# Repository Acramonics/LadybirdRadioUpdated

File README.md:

Making a Transistor Radio
=========================

Acramonics 2026
---------------

The Ladybird book *Making a Transistor Radio* by G.C. Dobbs with
wonderful illustrations by B.H. Robinson was first published in 1972
and reissued as a facsimile in 2008. The book goes through the
construction of the radio in stages, starting with a crystal set,
adding a single transistor amplifier, followed by a second transistor
amplifier. Finally, the radio frequency stage is improved through
'regeneration' using a third transistor to improve sensitivity.

Back around 1974, aged 10, I made this radio and it worked well for
me. It seems that others didn't have as much luck, particularly with
the final stage which was susceptible to oscillation - I suspect this
was a result of variation between samples of the transistors.  The
transistors used were PNP germanium types and are now very difficult
to obtain as they are no longer produced.  When you can find them,
they are very expensive as they are popular for guitar effects pedals.

As a result of these problems, @AndyDoz on YouTube has modified the
design to use easily-obtained silicon NPN transistors requiring the
power rails to be swapped over. Other small changes have been
introduced to reduce the chance of oscillation, adding a separate coil
for the regeneration stage and introducing emitter resistors as well
as modifying the transistor biasing to suit the silicon transistors. 

He has tried to replicate the original design as much as possible
including the use of a wooden board and brass screws with screwcups to
connect the components. Doz is providing a series of videos on YouTube
documenting the project.

- https://www.youtube.com/watch?v=Zk2TwEWvFMoz

My project takes Doz's design and ports it to a PCB. The first stage
will be a PCB for the full radio with regeneration. I will then modify
the PCB to allow each stage (crystal set, one-transistor and
two-transistor amplifiers) to be built on the same PCB.

**Note!** I would not normally design a PCB like this! The idea is to
make this as close to the layout of the circuit diagram and the wooden
board version as possible with each section clearly delineated.

Parts
-----

Doz has, of course fixed the problem of obtaining the transistors, but
the variable capacitor, radio frequency choke and transformer can be
problematic.

### Germanium diode

These are quite difficult to obtain - any germanium diode will do and
you should be able to find them on EBay. Amazon also sells 1N34A
germanium diodes as do Cricklewood and BitsBox.

You can still build the full regeneration stage radio without the diode.

### Earpiece

You need a high impedance earpiece, typically a so-called 'crystal
earphone'.  These are somewhat harder to find than they once were, but
are available from EBay, Rapid Electronics, CPC and Amazon.

### Sockets

There are **Molex 254** 'pin headers' indicated at various places on
the board; you then connect wires using a special housing. You do not
have to use these, you can simply push wires through the holes
instead. However, I recommend sockets for the two earpiece headers and
the loudspeaker as you will be adding and removing these (particularly
if you want to be able to go back to an earlier stage of the radio).

### Jumpers

These are all 2-row parts with 0.1" spacing. They are then fitted with
the little plastic headers that are used in computers. If you can't
find them, you can solder a wire across instead, but it does make
things more difficult as you will have to remove jumpers as well. If
simply progressing through the stages (and don't want to go back
again) you could just cut the wire jumpers off.

On the board, the jumpers (J1-J5) are marked at each position with the
characters X,1,2,G standing for crystal, 1-transistor, 2-transistor
and reGeneration respectively:

Jumper | Marking | Meaning
:----- | :------ | :----------------------------------------------------
J1:    | G       | Connect for regeneration
       | G       | Connect for regeneration
       | X12     | Connect for crystal, 1-transistor, and 2-transistor (not
       |         | regeneration)
       |         |    
J2:    | 12      | Connect for 1-transistor and 2-transistor (not crystal or
       |         | regeneration)
       | X       | Connect for crystal
       |         |    
J3:    | 12G     | Connect for 1-transistor, 2-transistor, and regeneration
       |         | (i.e. everything except the crystal set)
       |         |    
J4:    | G       | Connect for regeneration stage only
       | G       | Connect for regeneration stage only
       | G       | Connect for regeneration stage only
       |         |    
J5:    | 2G      | Connect for 2-transistor and regeneration (not for crystal
       |         | or 1-transistor
       | 2G      | Connect for 2-transistor and regeneration (not for crystal
       |         | or 1-transistor
       | 2G      | Connect for 2-transistor and regeneration (not for crystal
       |         | or 1-transistor

### Variable capacitor

The style of variable capacitor used in the book is almost
unobtainable.  The best replacement seems to be an AM+FM radio quad
PVC film variable capacitor containing dual 270pF and dual 20pF
variable capacitors. Wiring the two 270pF capacitors in parallel will
then give 540pF which is close enough to the specified 500pF. These
are available from various suppliers on AliExpress as the **CBM-443BF**
(and at varying prices - from about &pound;1.70 to &pound;16.50!).
There are variations available with different length shafts,
screw-trimmers, etc. Just look for the dual 270pF.

### Radio frequency choke

The RFC used in the book isn't made any more, but was a ferrite core
2.5mH device. The board leaves enough space for one of these if you
can find it, but it isn't a critical component, so a standard
resistor-like 2.2mH (2200uH) inductor should be fine.

### LT700 transformer

These are apparently still made and available from Cricklewood
Electronics, but I ordered one on EBay and instead was sent an Eagle
P631T. The P631T is easy to obtain from EBay and Amazon, 
YourSpares.co.uk, and audiomate.co.uk

The LT700 has a 1.2K primary with a centre tap (which is not used in
the Ladybird Radio) and a 3.2R secondary.  The P631T also has a 1.2K
primary (but with no centre tap) but has a 6.4R secondary with a
centre tap. Consequently, using one end and the centre tap will give
us the 3.2R we need.

The Xicon 42TL003-RC (available from Mouser) would probably work, but
has an 8R secondary (with centre tap) allowing a 4R secondary.

The Hammond 146J (available from Mouser) would probably also work, but
has a primary impedance of 1K instead of 1.2K.

The Tamura MET-23 (available from Mouser) has a 1.6K primary (with
centre tap) and a 3.2R secondary and would almost certainly be fine.

The board is configured for the P631T (since that is what I obtained),
but has a solder pad jumper to allow transformers which have 3.2R
secondaries without a centre-tap to be used. So if you are using an
LT700, 147J or MET-23, just bridge this jumper with some solder.

In all cases, the centre tap (of present) would be cut off the primary.

Model            | Primary   | Secondary 
:----------------|:----------|:-------------
Eagle LT700      | 1.2k CT   |  3.2R     
Eagle P631T      | 1.2k      |  6.4R CT  
Xicon 42TL003-RC | 1.2k CT   |  8R CT    
Hammond 146J     | 1.0k CT   |  3.2R     
Tamura MET-23    | 1.6k CT   |  3.2R     

(CT = centre tapped)

Construction
------------

### The ferrite rod coil

### The crystal set

- Populate the parts for the crystal set which are all in the `DETECTOR'
area of the board.

- Add the `X' jumpers for J1 and J2

- Connect an earpiece to the header in the `DETECTOR` part of the
  board. (You can just solder wires in, but you will have to remove
  them for later stages.)

- You will need a long aerial (about 100ft long) and a good earth
  connection (e.g. to a central heating or water pipe).

### The 1-transistor stage

- Add the components in the `1st TRANSISTOR` area of the board.

- Remove the jumpers that are just labelled `X'

- Add the `1' jumpers at J1, J2 and J3.

- Connect an earpiece to the header in the `1st TRANSISTOR` part of
  the board. (You can just solder wires in, but you will have to
  remove them for later stages.)

- Connect the battery and switch at the far right of the board

### The 2-transistor stage

- Add the components in the `2nd TRANSISTOR` area of the board.

- Remove any jumpers that are *not* labelled `2'

- Add the `2' jumpers at J1, J2, J3 and J5

- Connect a 4 Ohm loudspeaker in the `2nd TRANSISTOR` part of the
  board.

### Regeneration

- Add the components in the `REGENERATION` area of the board.

- Remove any jumpers that are *not* labelled `G'

- Add the `G' jumpers at J1, J3, J4 and J5

- You shouldn't need the aerial or earth connection any more!

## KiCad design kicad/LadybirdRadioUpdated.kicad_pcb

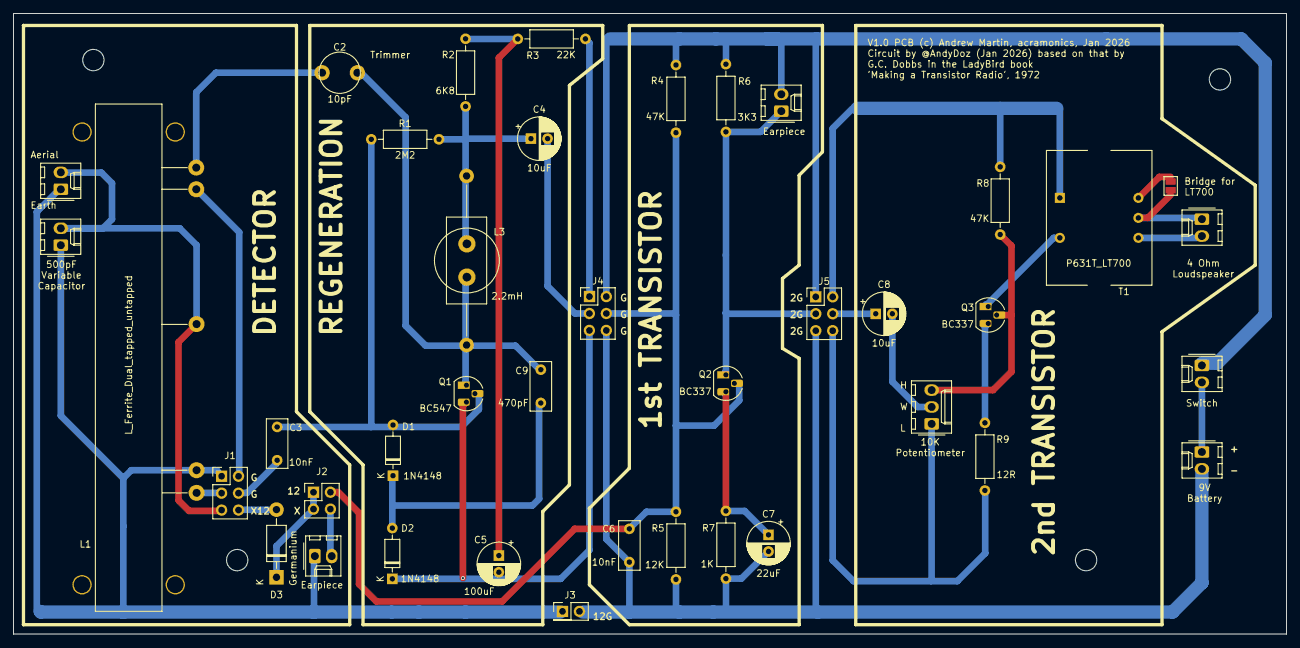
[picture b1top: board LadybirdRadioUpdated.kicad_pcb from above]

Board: 2 copper layers, 191.2 x 93.2 mm, 40 parts (0 on the bottom side), 33 nets.

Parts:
C2: 10pF; C_Trimmer_THT
C3, C6: 10nF; C_Rect_L7.2mm_W3.0mm_P5.00mm_FKS2_FKP2_MKS2_MKP2
C4, C8: 10uF; CP_Radial_D6.3mm_P2.50mm
C5: 100uF; CP_Radial_D6.3mm_P2.50mm
C7: 22uF; CP_Radial_D6.3mm_P2.50mm
C9: 470pF; C_Rect_L7.2mm_W3.0mm_P5.00mm_FKS2_FKP2_MKS2_MKP2
D1, D2: 1N4148; D_DO-35_SOD27_P7.62mm_Horizontal
D3: Germanium; D_DO-41_SOD81_P10.16mm_Horizontal
J1, J4, J5: Conn_02x03_Odd_Even; PinHeader_2x03_P2.54mm_Vertical
J2: Conn_02x02_Odd_Even; PinHeader_2x02_P2.54mm_Vertical
J3: Conn_02x01; PinHeader_2x01_P2.54mm_Vertical
J11: A/E; Molex_KK-254_AE-6410-02A_1x02_P2.54mm_Vertical
J12: VCap; Molex_KK-254_AE-6410-02A_1x02_P2.54mm_Vertical
J13, J14, J16, J17, J18: Conn_01x02_Pin; Molex_KK-254_AE-6410-02A_1x02_P2.54mm_Vertical
J15: Conn_01x03_Pin; Molex_KK-254_AE-6410-03A_1x03_P2.54mm_Vertical
JP1: SolderJumper_2_Open; SolderJumper-2_P1.3mm_Open_Pad1.0x1.5mm
L1: L_Ferrite_Dual_tapped_untapped; FerriteRod_L76.2mm_D10.0mm Tapped_25mm Untapped 10mm
L3: 2.2mH; L_Axial_L12.8mm_D5.8mm_P25.40mm_Horizontal_Radial_D9.5mm_P5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
Q1: BC547; TO-92_HandSolder
Q2, Q3: BC337; TO-92_HandSolder
R1: 2M2; R_Axial_DIN0207_L6.3mm_D2.5mm_P10.16mm_Horizontal
R2: 6K8; R_Axial_DIN0207_L6.3mm_D2.5mm_P10.16mm_Horizontal
R3: 22K; R_Axial_DIN0207_L6.3mm_D2.5mm_P10.16mm_Horizontal
R4, R8: 47K; R_Axial_DIN0207_L6.3mm_D2.5mm_P10.16mm_Horizontal
R5: 12K; R_Axial_DIN0207_L6.3mm_D2.5mm_P10.16mm_Horizontal
R6: 3K3; R_Axial_DIN0207_L6.3mm_D2.5mm_P10.16mm_Horizontal
R7: 1K; R_Axial_DIN0207_L6.3mm_D2.5mm_P10.16mm_Horizontal
R9: 12R; R_Axial_DIN0207_L6.3mm_D2.5mm_P10.16mm_Horizontal
T1: P631T_LT700; Transformer_P631T

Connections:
/+ve: J4.2, J5.1, J14.2, J18.1, R4.1, R6.1
/GND2: C6.2, C7.2, J3.2, J4.6, J5.5, J17.2, R5.2, R7.2
GND: J1.1, J3.1, J11.1, J12.1, J13.1, L1.2
unnamed: C2.1, L1.5
unnamed: C4.1, L3.1, R1.2, R2.1
unnamed: C5.1, R2.2, R3.2
unnamed: C3.2, D1.2 (A), Q1.2 (B), R1.1
unnamed: C9.2, D1.1 (K), D2.2 (A)
unnamed: C5.2, D2.1 (K), J4.5, Q1.3 (E)
unnamed: D3.2 (A), J1.6
unnamed: D3.1 (K), J2.1, J2.3
unnamed: J1.2, L1.4
unnamed: J1.3, L1.1
unnamed: C3.1, J1.4
unnamed: J1.5, J11.2, J12.2, L1.3
unnamed: C6.1, J2.2, J4.4, Q2.2 (B), R4.2, R5.1
unnamed: J4.1, R3.1
unnamed: C4.2, J4.3
unnamed: J5.2, R8.1, T1.1 (AA)
unnamed: C8.1, J5.4
unnamed: J2.4, J13.2
unnamed: J5.3, J14.1, Q2.1 (C), R6.2
unnamed: J5.6, J15.1, R9.2
unnamed: C8.2, J15.2
unnamed: J15.3, Q3.2 (B), R8.2
unnamed: J16.1, JP1.2 (B), T1.4 (SC)
unnamed: J16.2, T1.3 (SA)
unnamed: J17.1, J18.2
unnamed: JP1.1 (A), T1.5 (SB)
unnamed: C2.2, C9.1, L3.2, Q1.1 (C)
unnamed: C7.1, Q2.3 (E), R7.1
unnamed: Q3.1 (C), T1.2 (AB)
unnamed: Q3.3 (E), R9.1

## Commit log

2026-01-05 Initial commit of schematic
2026-01-05 Added README
2026-01-06 Added sockets and footprints
2026-01-06 Initial board design
2026-01-07 Fixed transformer; Fixed temporary C-trimmer; Tidied ferrite; Tidied labels and values on silk screen
2026-01-07 Added compnent information|
2026-01-13 Updated footprint for trimmer
2026-01-14 Added options for crystal set
2026-01-15 Separated out so this is just Crystal and Onetransistor
2026-01-16 Added second transistor
2026-01-16 Initial version with regen attached
2026-01-16 Full version completed
2026-01-16 PCB done but needs annotating
2026-01-19 Added board annotation and expanded readme
2026-01-23 Adjusted all labels to be the right way up and added Gerber files
2026-01-23 Some final tweaks and first version ready
